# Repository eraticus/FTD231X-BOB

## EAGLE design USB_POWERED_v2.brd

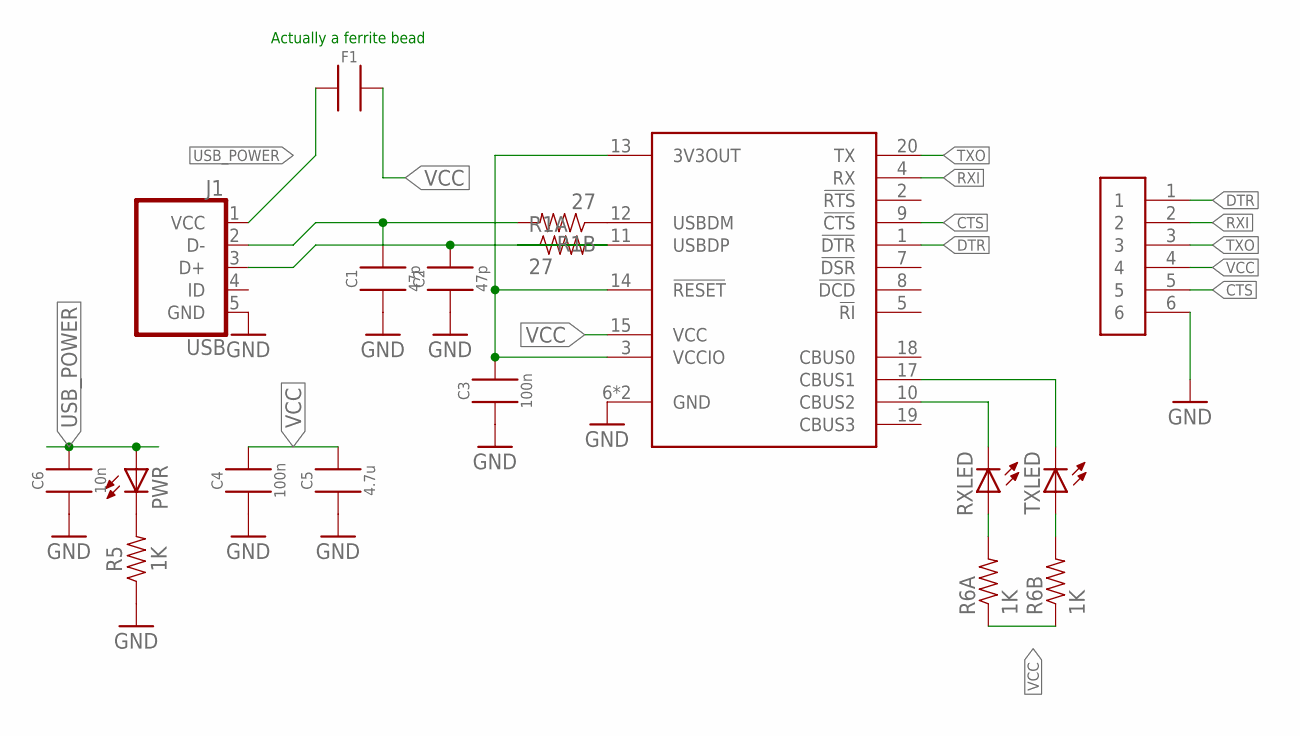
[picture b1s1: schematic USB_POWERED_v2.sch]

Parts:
C1, C2: 47p; 0603_A
C3, C4: 100n; 0603_A
C5: 4.7u; 0603_A
C6: 10n; 0603_A
F1: CAP0603A; 0603_A
J1: USB; 629105136821
PWR: LEDCHIP-LED0805; CHIP-LED0805
R1: 27; RESISTOR_ARRAY_CTS_742_4
R5: 1K; 0603
R6: 1K; RESISTOR_ARRAY_CTS_742C043
RXLED: LEDCHIP-LED0805; CHIP-LED0805
TXLED: LEDCHIP-LED0805; CHIP-LED0805
U$1: FT231XSSOP; SSOP-20
U$2: M06; M20_6_PIN

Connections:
3V3OUT: C3.2, U$1.3 (VCCIO), U$1.13 (3V3OUT), U$1.14 (!RESET)
CTS: U$1.9 (!CTS), U$2.5
DTR: U$1.1 (!DTR), U$2.1
GND: C1.1, C2.1, C3.1, C4.1, C5.1, C6.1, J1.5 (GND), R5.1, U$1.6 (GND), U$1.16 (GND), U$2.6
unnamed: R1.P$3 (1), U$1.12 (USBDM)
unnamed: R1.P$1 (1), U$1.11 (USBDP)
unnamed: PWR.C, R5.2
unnamed: C1.2, J1.2 (D-), R1.P$4 (2)
unnamed: C2.2, J1.3 (D+), R1.P$2 (2)
unnamed: R6.P$6 (2), TXLED.A
unnamed: R6.P$4 (2), RXLED.A
unnamed: RXLED.C, U$1.10 (CBUS2)
unnamed: TXLED.C, U$1.17 (CBUS1)
RXI: U$1.4 (RX), U$2.2
TXO: U$1.20 (TX), U$2.3
USB_POWER: C6.2, F1.1, J1.1 (VCC), PWR.A
VCC: C4.2, C5.2, F1.2, R6.P$3 (1), R6.P$5 (1), U$1.15 (VCC), U$2.4

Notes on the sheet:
Actually a ferrite bead

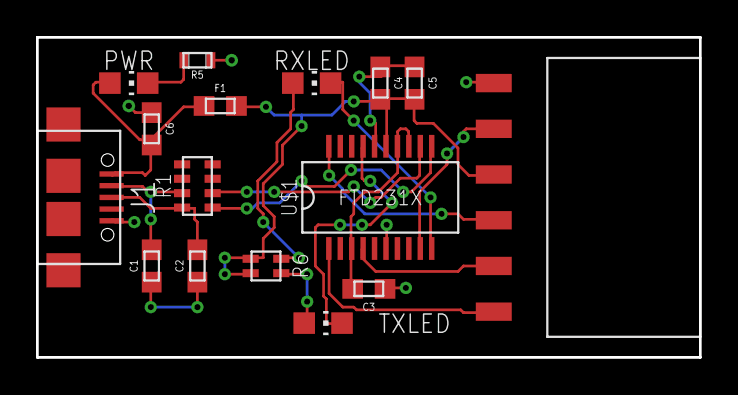
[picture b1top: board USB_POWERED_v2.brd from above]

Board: 2 copper layers, 36.8 x 17.8 mm, 16 parts (0 on the bottom side), 17 nets.

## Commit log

2017-09-15 Add Eagle files to project
2017-09-15 update routing. Will probably change again before file is sent...
